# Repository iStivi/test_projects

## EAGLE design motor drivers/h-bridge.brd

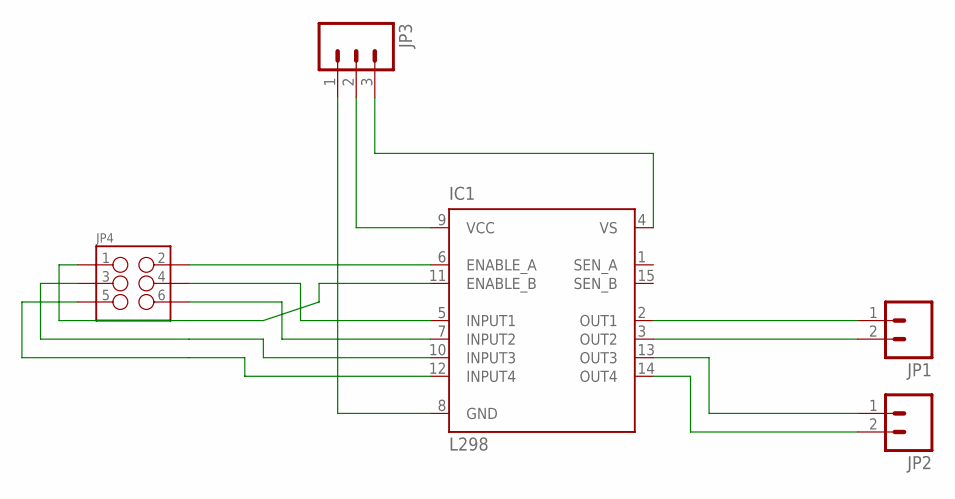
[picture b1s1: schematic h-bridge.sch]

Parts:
IC1: L298; MULTIWATT-15
JP1, JP2: M023.5MM; SCREWTERMINAL-3.5MM-2
JP3: M03SCREW; SCREWTERMINAL-3.5MM-3
JP4: M03X22X3_SILK_SM; 2X3

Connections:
A_1: IC1.5 (INPUT1), JP4.4
A_2: IC1.7 (INPUT2), JP4.6
A_EN: IC1.6 (ENABLE_A), JP4.2
A_OUT1: IC1.2 (OUT1), JP1.1
A_OUT2: IC1.3 (OUT2), JP1.2
B_1: IC1.10 (INPUT3), JP4.3
B_2: IC1.12 (INPUT4), JP4.5
B_EN: IC1.11 (ENABLE_B), JP4.1
B_OUT1: IC1.13 (OUT3), JP2.1
B_OUT2: IC1.14 (OUT4), JP2.2
GND: IC1.8 (GND), JP3.1
VCC: IC1.9 (VCC), JP3.2
VS: IC1.4 (VS), JP3.3

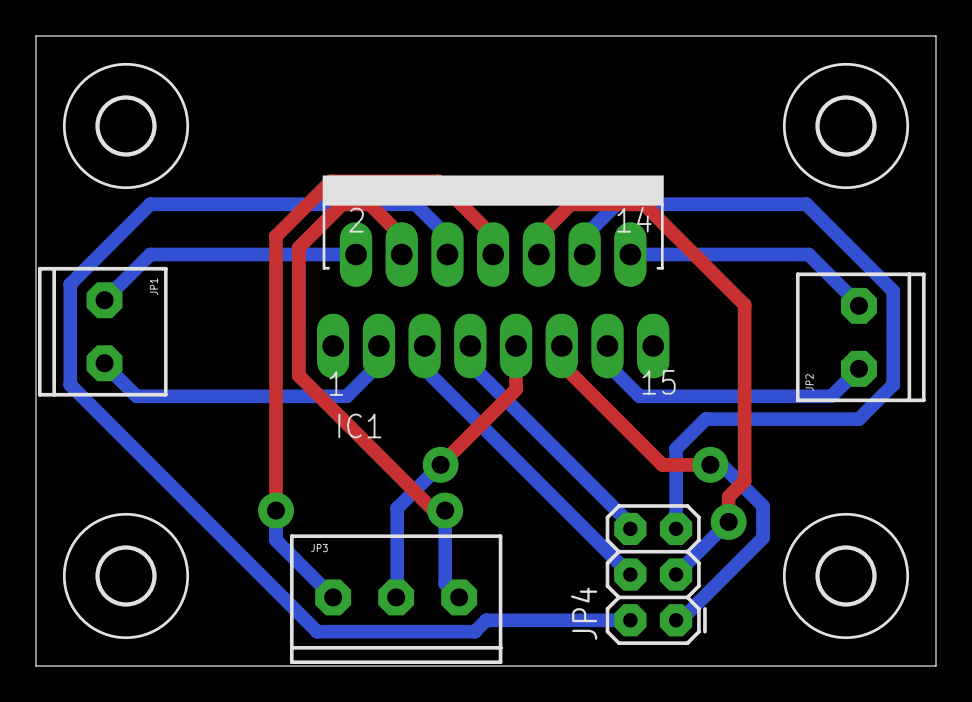
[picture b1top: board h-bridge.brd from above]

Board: 2 copper layers, 50.0 x 35.0 mm, 9 parts (0 on the bottom side), 13 nets.

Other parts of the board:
U$1, U$2, U$3, U$4: 3,0
